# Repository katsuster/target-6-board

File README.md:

# target-6-board

`target-6` is an opensource steel targets shooting game.

This is CAD data for I/O board to connect the server board with sensors of steel targets.

Please refer these repositories if you have interest in other modules of `target-6`.

* Client: https://github.com/katsuster/target-6-client
* Server: https://github.com/katsuster/target-6-server

## Requires

* Software
  * KiCad 7.0

## How to use

## Source structures

* ctrl/
  * For controller board
  * Begin or cancel the game by the push button
  * Notify start/end of the game by the beep buzzer
* io/
  * For main board
  * Connect server boards (ex. M5Stamp C3), controller and sensor boards
* sensor/
  * For sensor board
  * Detect the hit of BB bullet on steel plate

## Other documents

* [Parts list](doc/parts_jlcpcb.md)

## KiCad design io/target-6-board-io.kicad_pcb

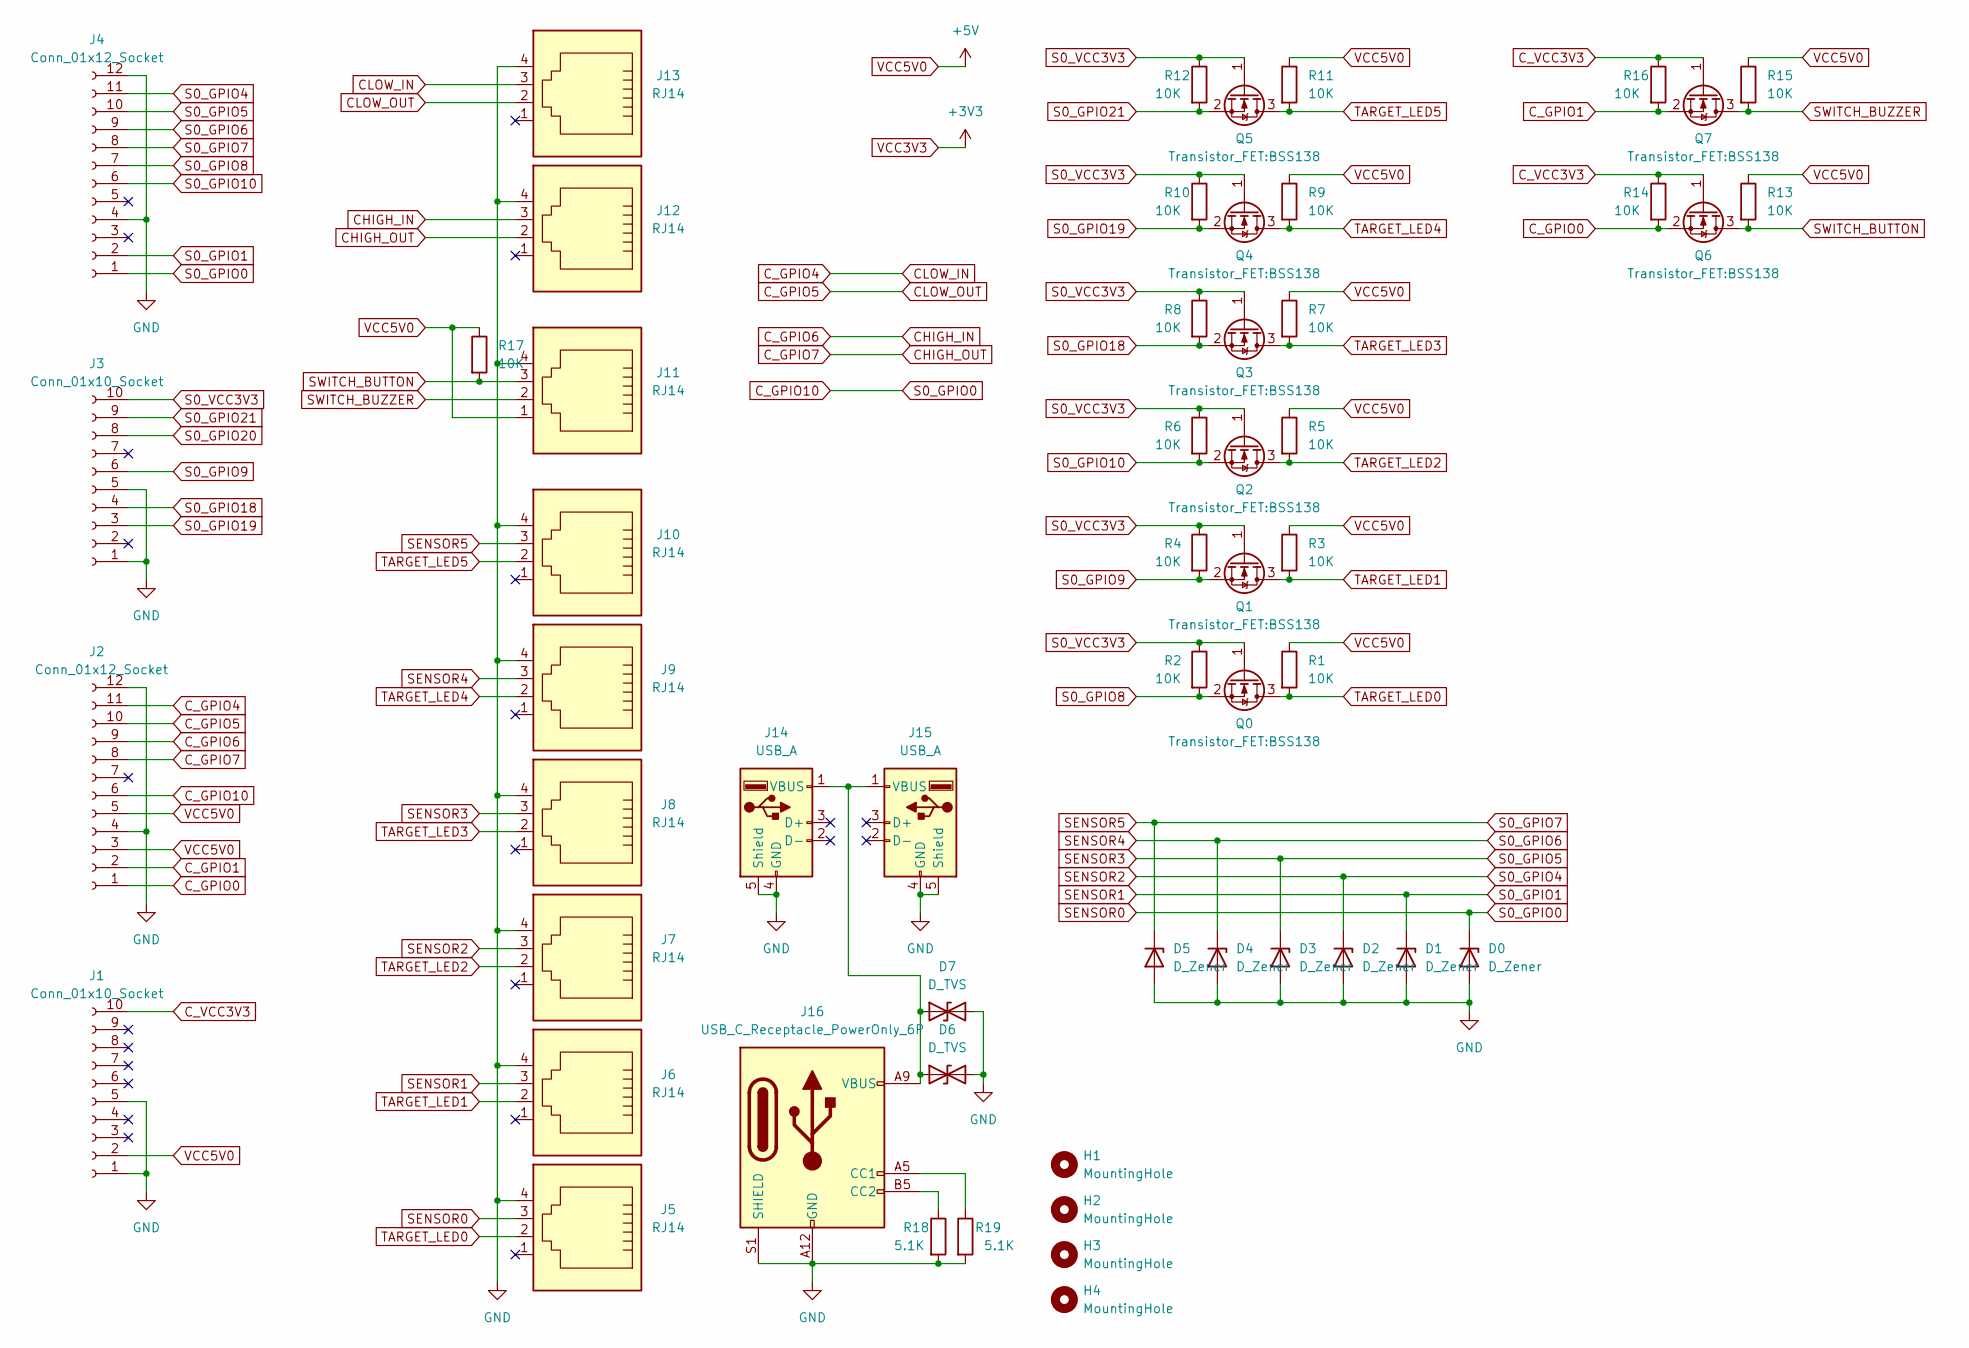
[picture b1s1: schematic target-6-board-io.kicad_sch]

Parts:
D0, D1, D2, D3, D4, D5: D_Zener; D_SOD-123
D6, D7: D_TVS; D_SOD-323
H1, H2, H3, H4: MountingHole; MountingHole_3.2mm_M3_ISO14580
J1, J3: Conn_01x10_Socket; PinHeader_1x10_P2.54mm_Vertical
J2, J4: Conn_01x12_Socket; PinHeader_1x12_P2.54mm_Vertical
J5, J6, J7, J8, J9, J10, J11, J12, J13: RJ14; RJ14_Connfly_DS1133-S4_Horizontal
J14, J15: USB_A; USB_A_Molex_67643_Horizontal
J16: USB_C_Receptacle_PowerOnly_6P; USB_C_Receptacle_GCT_USB4125-xx-x_6P_TopMnt_Horizontal
Q0, Q1, Q2, Q3, Q4, Q5, Q6, Q7: Transistor_FET:BSS138; SOT-23
R1, R2, R3, R4, R5, R6, R7, R8, R9, R10, R11, R12, R13, R14, R15, R16, R17: 10K; R_0603_1608Metric
R18, R19: 5.1K; R_0603_1608Metric

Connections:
CHIGH_IN: J2.9, J12.3
CHIGH_OUT: J2.8, J12.2
CLOW_IN: J2.11, J13.3
CLOW_OUT: J2.10, J13.2
C_GPIO0: J2.1, Q6.2 (S), R14.2
C_GPIO1: J2.2, Q7.2 (S), R16.2
C_GPIO10: D0.1 (K), J2.6, J4.1, J5.3
C_VCC3V3: J1.10, Q6.1 (G), Q7.1 (G), R14.1, R16.1
GND: D0.2 (A), D1.2 (A), D2.2 (A), D3.2 (A), D4.2 (A), D5.2 (A), D6.2 (A2), D7.2 (A2), J1.1, J1.5, J2.4, J2.12, J3.1, J3.5, J4.4, J4.12, J5.4, J6.4, J7.4, J8.4, J9.4, J10.4, J11.4, J12.4, J13.4, J14.4 (GND), J14.5 (Shield), J15.4 (GND), J15.5 (Shield), J16.A12 (GND), J16.B12 (GND), J16.S1 (SHIELD), R18.2, R19.2
unnamed: D6.1 (A1), D7.1 (A1), J14.1 (VBUS), J15.1 (VBUS), J16.A9 (VBUS), J16.B9 (VBUS)
unnamed: J16.A5 (CC1), R19.1
unnamed: J16.B5 (CC2), R18.1
S0_GPIO1: D1.1 (K), J4.2, J6.3
S0_GPIO4: D2.1 (K), J4.11, J7.3
S0_GPIO5: D3.1 (K), J4.10, J8.3
S0_GPIO6: D4.1 (K), J4.9, J9.3
S0_GPIO7: D5.1 (K), J4.8, J10.3
S0_GPIO8: J4.7, Q0.2 (S), R2.2
S0_GPIO9: J3.6, Q1.2 (S), R4.2
S0_GPIO10: J4.6, Q2.2 (S), R6.2
S0_GPIO18: J3.4, Q3.2 (S), R8.2
S0_GPIO19: J3.3, Q4.2 (S), R10.2
S0_GPIO20: J3.8
S0_GPIO21: J3.9, Q5.2 (S), R12.2
S0_VCC3V3: J3.10, Q0.1 (G), Q1.1 (G), Q2.1 (G), Q3.1 (G), Q4.1 (G), Q5.1 (G), R2.1, R4.1, R6.1, R8.1, R10.1, R12.1
SWITCH_BUTTON: J11.3, Q6.3 (D), R13.2, R17.2
SWITCH_BUZZER: J11.2, Q7.3 (D), R15.2
TARGET_LED0: J5.2, Q0.3 (D), R1.2
TARGET_LED1: J6.2, Q1.3 (D), R3.2
TARGET_LED2: J7.2, Q2.3 (D), R5.2
TARGET_LED3: J8.2, Q3.3 (D), R7.2
TARGET_LED4: J9.2, Q4.3 (D), R9.2
TARGET_LED5: J10.2, Q5.3 (D), R11.2
VCC5V0: J1.2, J2.3, J2.5, J11.1, R1.1, R3.1, R5.1, R7.1, R9.1, R11.1, R13.1, R15.1, R17.1

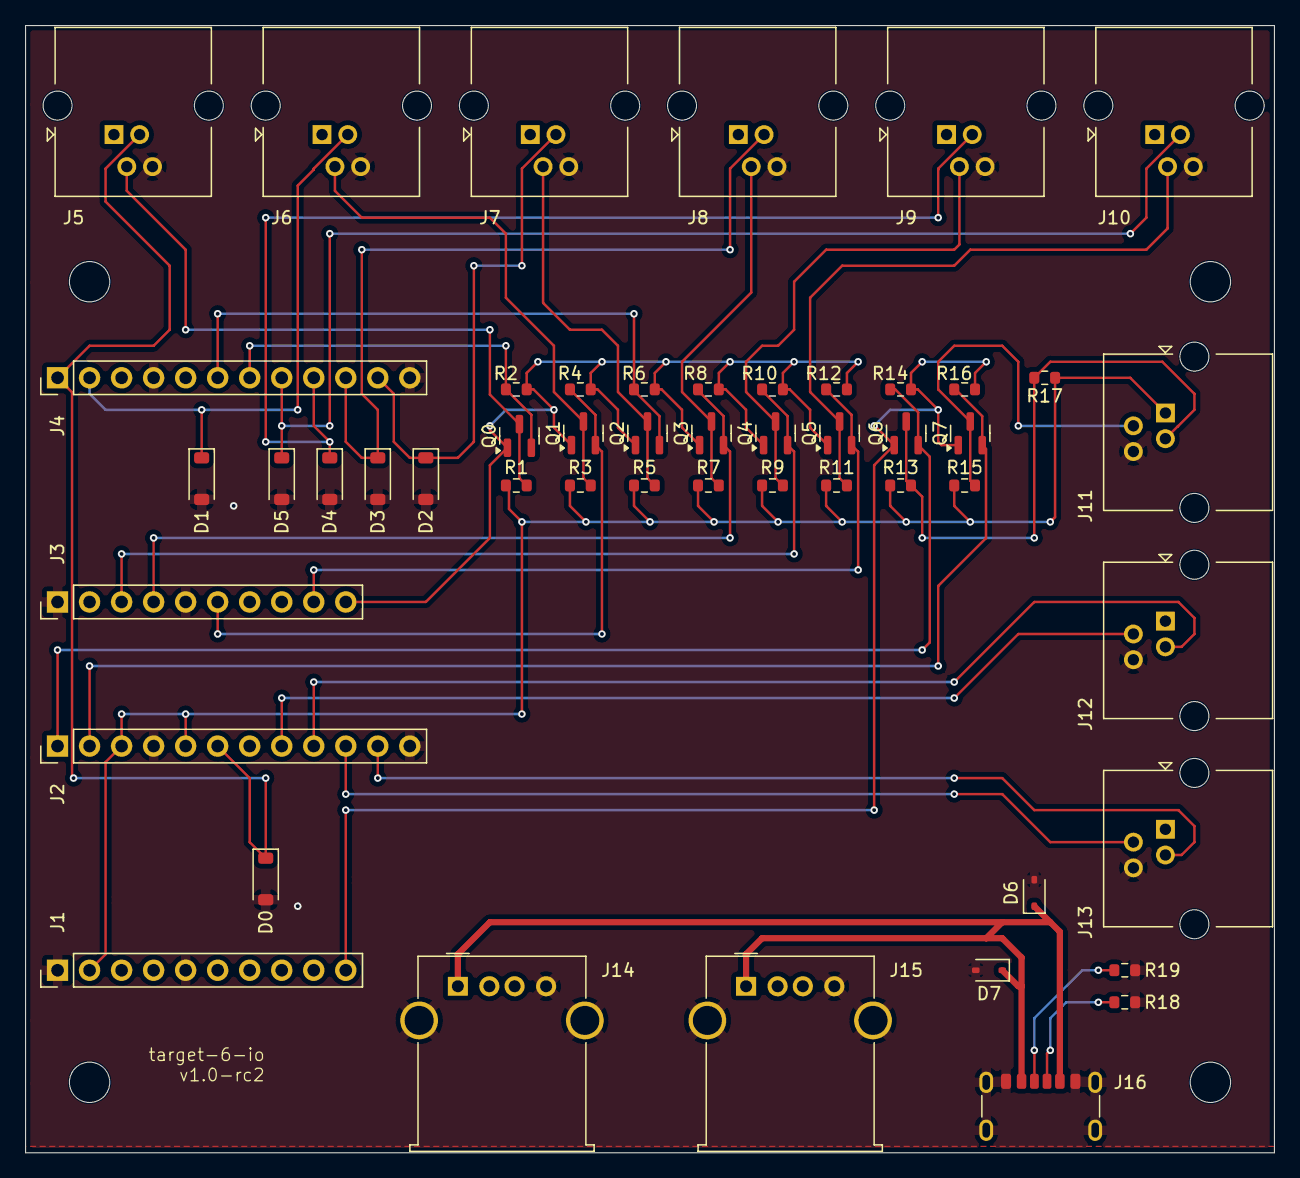
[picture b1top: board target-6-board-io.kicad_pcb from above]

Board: 2 copper layers, 99.1 x 89.4 mm, 55 parts (0 on the bottom side), 33 nets.

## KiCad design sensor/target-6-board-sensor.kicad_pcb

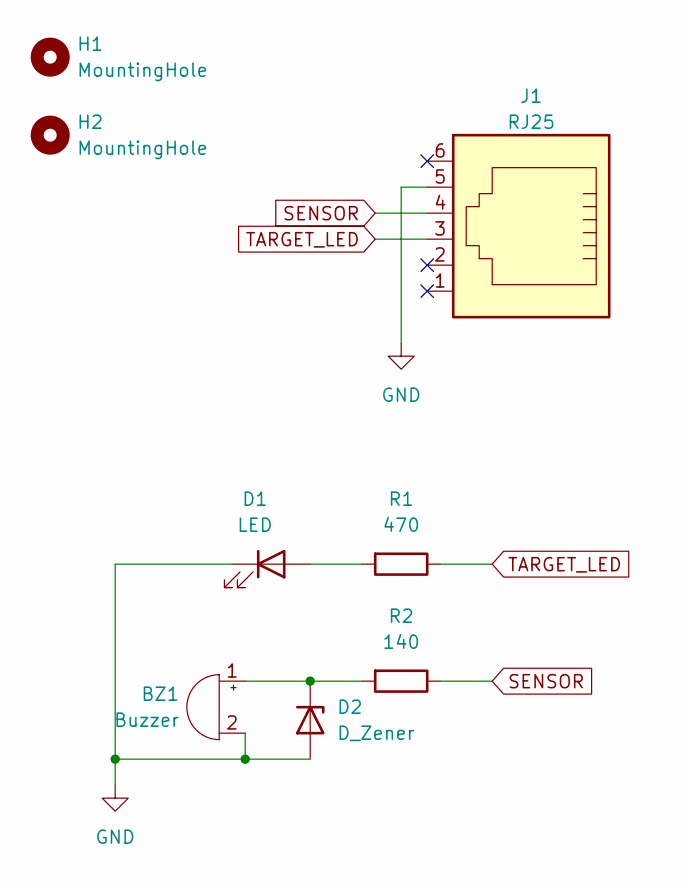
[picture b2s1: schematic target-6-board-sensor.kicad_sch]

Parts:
BZ1: Buzzer; Buzzer_15x7.5RM7.6
D1: LED; LED_D5.0mm
D2: D_Zener; D_DO-35_SOD27_P7.62mm_Horizontal
H1, H2: MountingHole; MountingHole_2.2mm_M2
J1: RJ25; RJ25_Wayconn_MJEA-660X1_Horizontal
R1: 470; R_Axial_DIN0207_L6.3mm_D2.5mm_P10.16mm_Horizontal
R2: 140; R_Axial_DIN0207_L6.3mm_D2.5mm_P10.16mm_Horizontal

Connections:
GND: BZ1.2 (-), D1.1 (K), D2.2 (A), J1.5
unnamed: BZ1.1 (+), D2.1 (K), R2.2
unnamed: D1.2 (A), R1.2
SENSOR: J1.4, R2.1
TARGET_LED: J1.3, R1.1

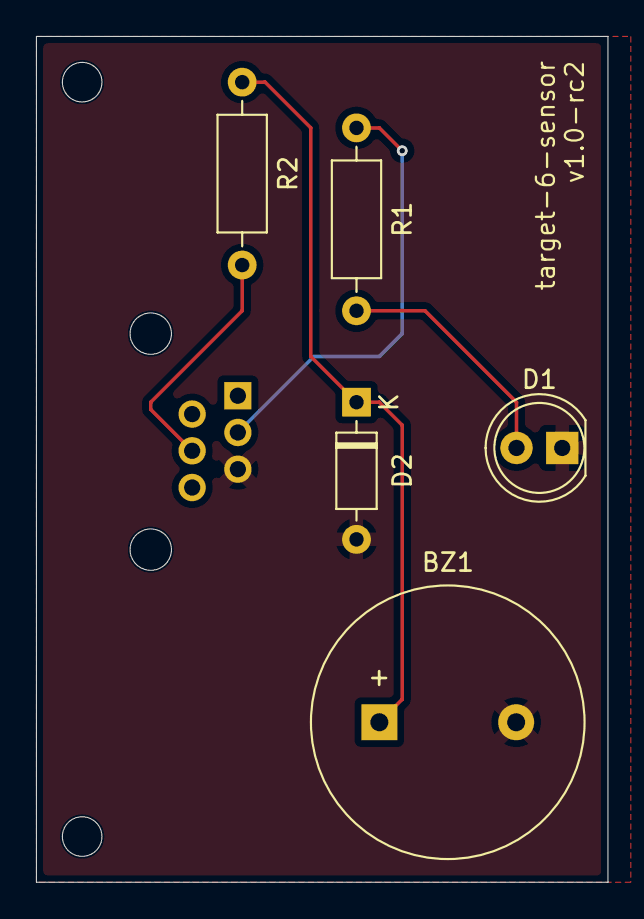
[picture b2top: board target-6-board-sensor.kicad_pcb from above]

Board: 2 copper layers, 31.8 x 47.0 mm, 8 parts (1 on the bottom side), 5 nets.

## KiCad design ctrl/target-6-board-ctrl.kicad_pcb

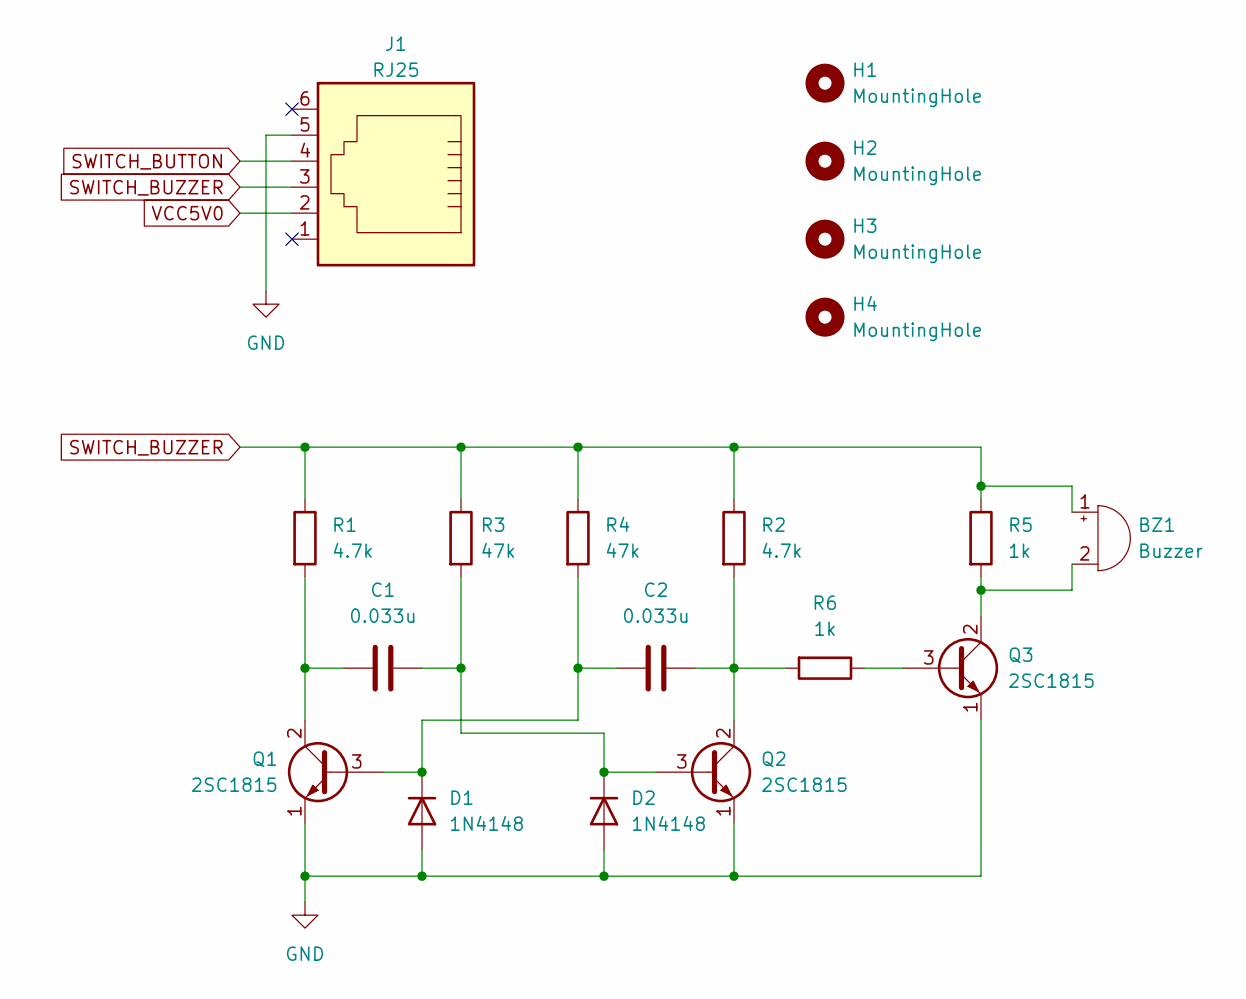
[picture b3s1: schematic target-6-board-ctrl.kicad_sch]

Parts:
BZ1: Buzzer; Buzzer_15x7.5RM7.6
C1, C2: 0.033u; C_Axial_L5.1mm_D3.1mm_P7.50mm_Horizontal
D1, D2: 1N4148; D_DO-35_SOD27_P7.62mm_Horizontal
H1, H2, H3, H4: MountingHole; MountingHole_3.2mm_M3
J1: RJ25; RJ25_Wayconn_MJEA-660X1_Horizontal
Q1, Q2, Q3: 2SC1815; TO-92_Inline
R1, R2: 4.7k; R_Axial_DIN0207_L6.3mm_D2.5mm_P7.62mm_Horizontal
R3, R4: 47k; R_Axial_DIN0207_L6.3mm_D2.5mm_P7.62mm_Horizontal
R5, R6: 1k; R_Axial_DIN0207_L6.3mm_D2.5mm_P7.62mm_Horizontal

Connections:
GND: D1.2 (A), D2.2 (A), J1.5, Q1.1 (E), Q2.1 (E), Q3.1 (E)
unnamed: BZ1.2 (-), Q3.2 (C), R5.2
unnamed: C2.2, D1.1 (K), Q1.3 (B), R4.2
unnamed: C1.1, D2.1 (K), Q2.3 (B), R3.2
unnamed: C1.2, Q1.2 (C), R1.2
unnamed: C2.1, Q2.2 (C), R2.2, R6.2
unnamed: Q3.3 (B), R6.1
SWITCH_BUTTON: J1.4
SWITCH_BUZZER: BZ1.1 (+), J1.3, R1.1, R2.1, R3.1, R4.1, R5.1
VCC5V0: J1.2

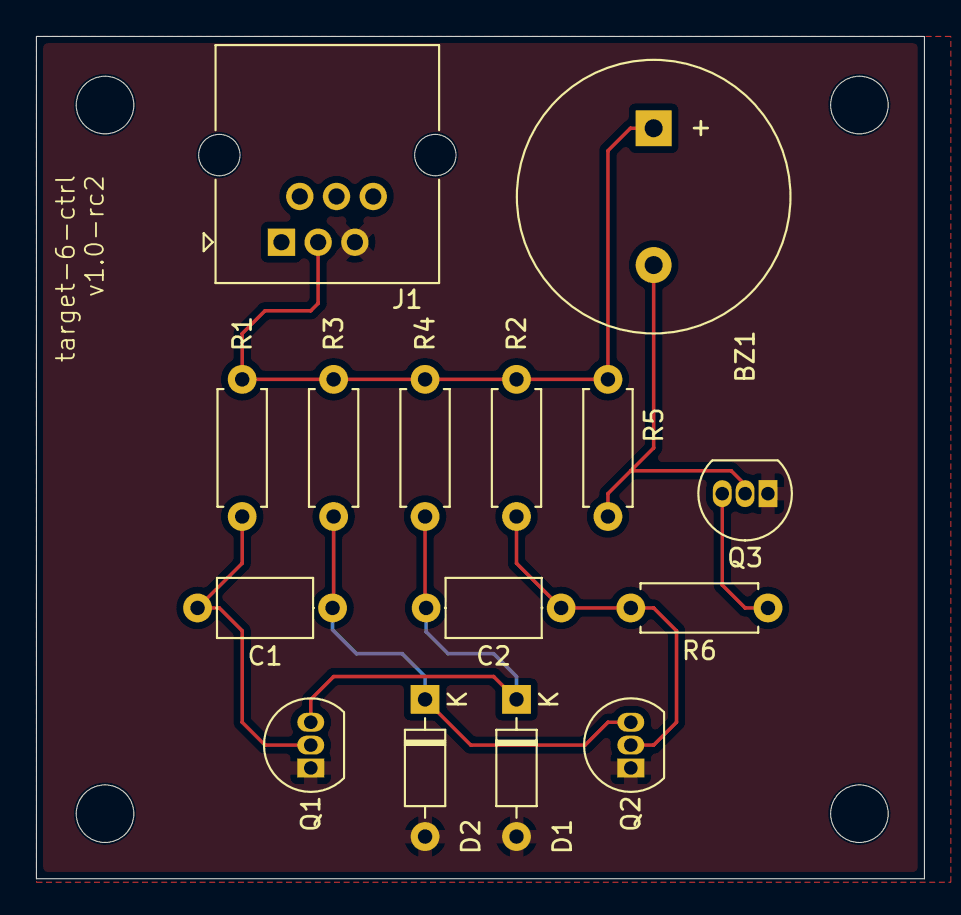
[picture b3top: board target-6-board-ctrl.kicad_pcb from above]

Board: 2 copper layers, 49.3 x 46.8 mm, 19 parts (0 on the bottom side), 8 nets.

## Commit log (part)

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2024-03-21 init
2024-03-21 first version
2024-03-24 PCB order version
    - Add USB connectors for power supply to M5Stamp C3
    - Add RJ14 connectors for multiplay
2024-03-24 doc: add parts list for 2024/03 order
2024-03-24 remove unused libs
2024-03-24 doc: add tag name of git
2024-03-24 doc: add README
2024-03-24 doc: add a simple project description to README
2024-04-05 add no connect flags
2024-04-06 fix NMOS type to BSS138 and PCB design
2024-05-02 io: move I/O boards into io/ directory
2024-05-02 ctrl: add an empty project
2024-05-02 sensor: add an empty project
2024-05-02 gitignore: add backup directories
2024-05-02 sensor: add first version
2024-05-05 sensor: change buzzer to 15mm from 12mm
2024-05-05 gitignore: add fp-info-cache
2024-05-06 doc: add source code structure
2024-05-17 io: shrink board edge and move mounting holes, pin headers
2024-05-17 ctrl: add astable multivibrator
2024-06-05 sensor: fix distance of mounting holes
2024-06-09 ctrl: changes for pruduction by Fabrication Toolkit plugin
2024-06-09 sensor: add board name and version
2024-06-09 ctrl: add mouting hole and board name and version
2024-06-09 io: add board name and version
2024-06-09 doc: add parts list for 2024/06 order
